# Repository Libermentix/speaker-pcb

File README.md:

# Speaker Pcb

## About This Project

This PCB is a work-in-progress and has not yet been tested.

The speaker PCB is based on the schematic used in the [Speaker Workshop by Freie Maker e.V. (in German).](https://freie-maker.de/2018/06/der-boxenbau-workshop-bei-den-freien-makern/) It adds three terminal blocks to make cabling inside the speaker a bit more robust (as cables won&#39;t have to be soldered anymore).

Additional documentation can be found [here](https://docs.google.com/document/d/1xRjg8uscsd9Le15cIWoDVk5CKfX-zGayms6dGGZDSWU/edit).

## Renderings

### Top

### Bottom

## BOM

|Count|Component|Details|Datasheet|
|-|-|-|-|
|3x|J1 / J2 / J3|CONN TERM BLOCK 45DEG 2POS 3.5MM|[Link](https://media.digikey.com/pdf/Data%20Sheets/Phoenix%20Contact%20PDFs/Combicon%20Compact%20Series.pdf)|

---

This project is managed and available on

You can view it [here](https://aisler.net/p/XABQRYWK). Start your own Powerful Prototype on [here](https://aisler.net).

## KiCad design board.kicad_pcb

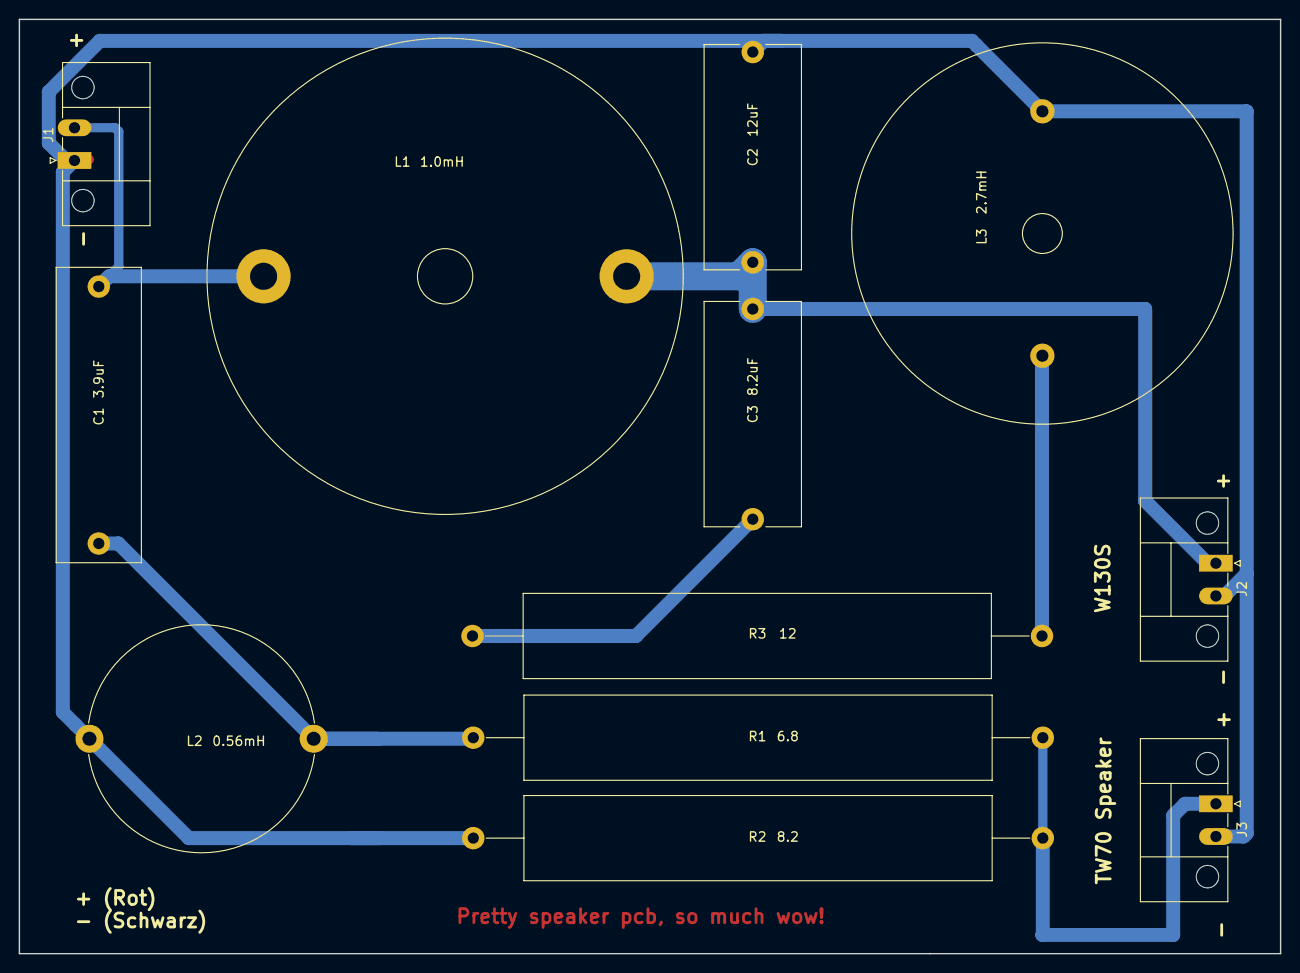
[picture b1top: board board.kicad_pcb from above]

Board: 2 copper layers, 135.0 x 100.0 mm, 12 parts (0 on the bottom side), 7 nets.

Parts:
C1: 3.9uF; C_Rect_L31.5mm_W9.0mm_P27.50mm_MKS4
C2: 12uF; C_Rect_L24.0mm_W10.3mm_P22.50mm_MKT
C3: 8.2uF; C_Rect_L24.0mm_W10.3mm_P22.50mm_MKT
J1, J2, J3: Conn_01x02; PhoenixContact_MC-GF_02x3.50mm_Angled_ThreadedFlange_MountH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
L1: 1.0mH; L_Radial_D50.8mm_P38.86mm_Vishay_IHB-6
L2: 0.56mH; L_Radial_D24.0mm_P24.00mm
L3: 2.7mH; L_Radial_D40.6mm_P26.16mm_Vishay_IHB-5
R1: 6.8; R_Axial_Power_L50.0mm_W9.0mm_P60.96mm
R2: 8.2; R_Axial_Power_L50.0mm_W9.0mm_P60.96mm
R3: 12; R_Axial_Power_L50.0mm_W9.0mm_P60.96mm

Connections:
unnamed: C1.1, L2.1, R1.2
unnamed: C1.2, J1.2, L1.2
unnamed: C2.1, C3.1, J2.1, L1.1
unnamed: C2.2, J1.1, J2.2, J3.2, L2.2, L3.2, R2.2
unnamed: C3.2, R3.1
unnamed: J3.1, R1.1, R2.1
unnamed: L3.1, R3.2

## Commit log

2018-07-23 Syncing AISLER project with GitHub repository
